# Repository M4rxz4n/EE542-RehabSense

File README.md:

# EE542-RehabSense
Rehab Sense Project for embedded systems capstone class

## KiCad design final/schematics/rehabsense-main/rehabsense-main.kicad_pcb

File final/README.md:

# RehabSense — final

Single-channel sEMG + dual-IMU armband for home-based stroke rehabilitation.
Built to PRD v1.4.

## What to flash, and what to run

```
firmware-s3/   ← FLASH THIS.  Arduino, ESP32-S3 / XIAO ESP32S3
app/           ← RUN THIS.    Flutter, iOS and Android
```

Everything else here is reference or tooling:

| Directory | What it is |
| --- | --- |
| `firmware-s3/` | **The shipping firmware.** `rehabsense_v5` retargeted from the ESP32 Dev Module to the ESP32-S3, on either of two wirings, with two haptic motors. All of FC1–FC6, FT1–FT4, AP1–AP2, GP1–GP3, AT1–AT4 |
| `app/` | **The shipping app.** Patient, calibration, session analysis, progress over time, therapist dashboard, developer tools |
| `firmware/` | The ESP-IDF tree: the PRD-shaped reference implementation. Kept for its design, its host test suites and its wire-format definitions. **Does not implement the step 1–5 behaviour**, so it is not what gets flashed |
| `python/` | The `bleak` host client and the offline analysis tools. Still the fastest way to capture raw data for tuning |
| `schematics/` | KiCad project for the custom PCB |

---

## Why there are two firmwares

The prototype firmware and the ESP-IDF firmware grew in parallel and diverged.

The **ESP-IDF tree** is architecturally what the PRD describes: tiered session
buffer in PSRAM, DSP chain with a mains notch and a median-frequency
estimator, a six-step calibration protocol, five host-side test suites. What
it does not have is any of the behaviour the demo actually shows — false-curl
rejection, fatigue indicators, auto-pause, guided pace, adaptive target.

The **prototype firmware** has all of that, and it is the only one that has
ever run on hardware with electrodes attached. So it is the one that ships,
retargeted to the S3. The ESP-IDF tree stays because its wire-format
definitions are the contract both halves are written against, and because its
design is the one the written documents describe.

They speak the same BLE protocol. That is what made the retarget tractable and
what lets the app, the HTML session viewer and `rehab_client.py` all talk to
either one.

---

## The three hosts, and when to use each

| Host | Good for | Needs |
| --- | --- | --- |
| **`app/`** (Flutter) | The demo. A session with a patient. Progress across visits | A phone |
| **HTML session viewer** (`../prototype/prototype demo final file/`) | Reading a recorded Serial Monitor log. Quick bench work next to a USB cable | Chrome or Edge |
| **`python/rehab_client.py`** | Capturing raw data for offline tuning — filter corners, thresholds, grading weights | A laptop and `pip install bleak` |

The app's Developer tab copies the sleeve's printed output to the clipboard in
exactly the viewer's input format, so a session recorded on the phone can be
read in the viewer afterwards.

---

## Getting from nothing to a working demo

1. **Flash.** `firmware-s3/README.md`. Arduino IDE, board `ESP32S3 Dev Module`
   for the breadboard. On the XIAO it is `XIAO_ESP32S3` plus
   **Tools → PSRAM → OPI PSRAM** — the default is Disabled and the boot log
   then reads `PSRAM 0 kB`, which looks exactly like a dead memory chip.
2. **Check the sleeve alone.** Serial Monitor at 115200. The banner prints the
   bus map it was built for, which is how you catch a board flashed for the
   other wiring. Both IMUs should report started; if one does not, the message
   names its bus, the address it tried, the clock it reached and which failure
   it saw.
3. **Check both motors.** Type `hm`. It says which DRV2605Ls answered and
   where each cue plays. A sleeve running on one motor keeps working and feels
   subtly wrong, so this is worth doing before anything else is judged.
4. **Check the signal.** Type `e` for the EMG test: 3 s relaxed, 3 s
   squeezing, then an SNR figure. Do this before trusting any effort
   percentage, and especially after the move from GPIO34 to GPIO4.
5. **Calibrate.** Type `c`, then `n` through the three steps, then `g`.
6. **Run the app.** `cd app && flutter pub get && flutter analyze &&
   flutter test`, then `flutter run`. Connect, and the Calibrate tab will walk
   the same three steps from the phone.

No sleeve to hand? The app's **demo mode** drives every screen with synthetic
frames and printed lines in the real wire formats.

---

## What has and has not been verified

Worth being precise about, because the two halves have been checked by very
different means.

**Firmware — compiled, not run.** Seven configurations build with zero errors
and zero warnings at `--warnings all` — two boards × two sensor buses × two
haptic topologies, minus the crossings nobody will build;
`firmware-s3/verify_build.sh` reproduces that from nothing. The default build
is the PCB's architecture. It has never been flashed. The second haptic channel is the
one piece of behaviour that is new rather than ported, so it is the first thing
to check on the bench: `hm` on the console says which DRV2605Ls answered.

**App — cross-checked, not compiled.** `flutter analyze` and `flutter test`
have not been run; there was no Dart toolchain where this was written. Instead
`app/tool/check_dart.py` verifies names, imports, members and constructor
arguments across all 41 files, and `app/tool/check_message_patterns.py`
verifies the printed-line parser against the firmware's own format strings.
Both run clean. **Run `flutter analyze && flutter test` before the demo.**

Measured, from the real builds:

| Build | Flash used | Static RAM used, of 327,680 B | Free for locals |
| --- | --- | --- | --- |
| S3 Dev Module, I2C x2 — **the breadboard** | 664,105 B (50%) | 40,092 B (12%) | 287,588 B |
| S3 Dev Module, SPI + TCA9543A — **the PCB** | 666,401 B (50%) | 40,092 B (12%) | 287,588 B |
| XIAO ESP32S3, I2C x2 | 634,116 B (18%) | 39,772 B (12%) | 287,908 B |
| XIAO, I2C x2, PSRAM OPI | 639,386 B (19%) | 40,248 B (12%) | 287,432 B |
| XIAO ESP32S3, SPI | 636,412 B (19%) | 39,772 B (12%) | 287,908 B |

The other two `verify_build.sh` compiles — the crossed haptic topologies — land
within 500 B of these. Static RAM does not move at all.

The XIAO is **not** a memory downgrade: its ESP32-S3R8 carries the same 512 KB
SRAM and 8 MB octal PSRAM as the DevKitC-1 N8R8. The firmware uses 12% of
static RAM and never touches PSRAM.

---

## Two wirings, one firmware

The PCB is the target; the breadboard is a bring-up configuration kept
alongside it. `pins.h` chooses at compile time and nothing above `imu.cpp`
knows which it got.

| | Custom PCB — the default | Breadboard |
| --- | --- | --- |
| Board | XIAO ESP32-S3 on a carrier | ESP32-S3-DevKitC-1 |
| IMUs | **one SPI bus**, a chip select each | **two I2C buses**, one each |
| Haptics | one bus + **TCA9543A** switch | two I2C buses |
| EMG | **ADS131M02** on SPI — *not yet driven* | MyoWare 2.0 on ADC1 |
| Build with | nothing | `-DRS_IMU_BUS=RS_IMU_I2C` |
| Source | `schematics/` | the wiring diagram of 1 Nov |
| Pin numbers | **provisional** — see below | from the diagram |

Both agree on two DRV2605Ls and two ERMs. The haptic topology follows the IMU
bus, so one flag selects the whole architecture.

Two I2C buses is not a preference: both BMI270 breakouts sit at 0x68 and the
DRV2605L's 0x5A has no address strap, so each bus can hold exactly one of
each.

The two motors also reach the MCU differently, and for the same reason: `0x5A`
is fixed on a DRV2605L, so two cannot answer on one bus. The breadboard gives
each its own bus. The PCB puts both behind a **TCA9543A** 2-channel I2C switch
— `haptic.kicad_sch` has one `TCA9543APWR`, two `DRV2605LDGST`s and the nets
`SDA_H1` / `SCL_H1` / `SDA_H2`, while `mcu.kicad_sch` brings out a single
`SDA` / `SCL` pair. `RS_HAPTIC_MUX` selects, and follows the IMU bus by
default, so neither board needs its own firmware.

| | Breadboard | Custom PCB |
| --- | --- | --- |
| Two DRV2605Ls reached by | two I2C buses | one bus + TCA9543A switch |
| `RS_HAPTIC_MUX` | 0 (default with I2C IMUs) | 1 (default with SPI IMUs) |

Still unmodelled, and still provisional: the SPI mode's **GPIO numbers** (the
schematic names nets, not readably pins), the **TCA9543A's strapped address**
(`haptic_begin()` scans 0x70–0x73 and reports which answered), and the PCB's
**external SPI ADC** (`CS_ADC`, `DRDY_ADC`), which would replace the MyoWare
going straight into ADC1. `mcu.kicad_sch` also uses the `XIAO_ESP32_S3`
symbol, so the PCB is a XIAO carrier board rather than a DevKitC. The I2C
mode is the one that matches wiring that exists.

## Pin map at a glance

Full reasoning in `firmware-s3/rehabsense_s3/pins.h`.

**ESP32-S3-DevKitC-1 — the breadboard, as drawn**

| Function | GPIO |
| --- | --- |
| I2C bus 0: upper-arm BMI270 `0x68` + DRV2605L `0x5A` → ERM M1 | SDA **8**, SCL **9** |
| I2C bus 1: forearm BMI270 `0x68` + DRV2605L `0x5A` → ERM M2 | SDA **17**, SCL **18** |
| MyoWare 2.0 ENV | **4** — ADC1_CH3 |
| Status LED, WS2812 | **48** (**38** on v1.1 — build `-DRS_LED_PIN=38`) |
| Start calibration | **0** (BOOT button) |
| Spare | **5** (MyoWare RAW), **6** |

One 4.7 kΩ pull-up per line per bus, to 3V3. Do not wire GPIO 0/3/45/46
(strapping), 19/20 (USB), 26–32 (flash), 33–37 (octal PSRAM), 43/44 (UART).

**XIAO ESP32S3 — the shipping sleeve.** Same build; only pins that leave the
module. Silkscreen in brackets.

| Function | GPIO |
| --- | --- |
| I2C bus 0 | SDA **5** [D4], SCL **6** [D5] |
| I2C bus 1 | SDA **8** [D9], SCL **9** [D10] |
| MyoWare 2.0 ENV | **4** [D3] |
| Status LED | **21** (plain, active LOW — the XIAO has no WS2812) |

Free on the XIAO: GPIO3 [D2] for the Phase 2 triceps channel, and GPIO43/44
[D6/D7].

On the PCB's SPI wiring each BMI270 breakout needs its **ADR jumper fully
open** — that is what selects SPI — and its I2C pull-ups cut. On the
breadboard the jumpers stay closed at 0x68 and the pull-ups stay.

---

## Open items

| Open | Blocked on |
| --- | --- |
| First flash, and a real BLE connection | A bench |
| Both BMI270s answering over SPI | A bench |
| **Any EMG at all on the PCB** | The ADS131M02 driver, which needs four numbers off the board. `ADC1` is unconnected there |
| Both DRV2605Ls answering — type `hm` | A bench. Two motors is new scope, not a port |
| Whether the pace beat belongs on the forearm alone | Someone wearing it. One column of the table in `haptic.cpp` |
| Whether the WS2812 is on GPIO48 or GPIO38 | Which DevKitC-1 revision is on the desk |
| The PCB's real pin assignment, and its external SPI ADC | Reading `schematics/`. The SPI mode's GPIO numbers are provisional and that board also moves the EMG off ADC1 |
| The TCA9543A path, and its strapped address | Never run. `haptic_begin()` scans 0x70–0x73 and says which answered |
| EMG levels on GPIO4 against the prototype's GPIO34 | Different ADC, different attenuation curve. Run `e` and compare |
| Elbow-angle accuracy | PRD gate: 5–10° against a goniometer at 0°, 45°, 90°, 135° |
| `flutter analyze` / `flutter test` | A machine with the Flutter SDK |
| Battery endurance | A two-hour run |
| Haptic feel on the final ERM | DRV2605L values carried over from a different motor mounting |
| Filter corners, thresholds, grading weights | Volunteer data. All settable over BLE at runtime, so tuning is a session rather than a rebuild |

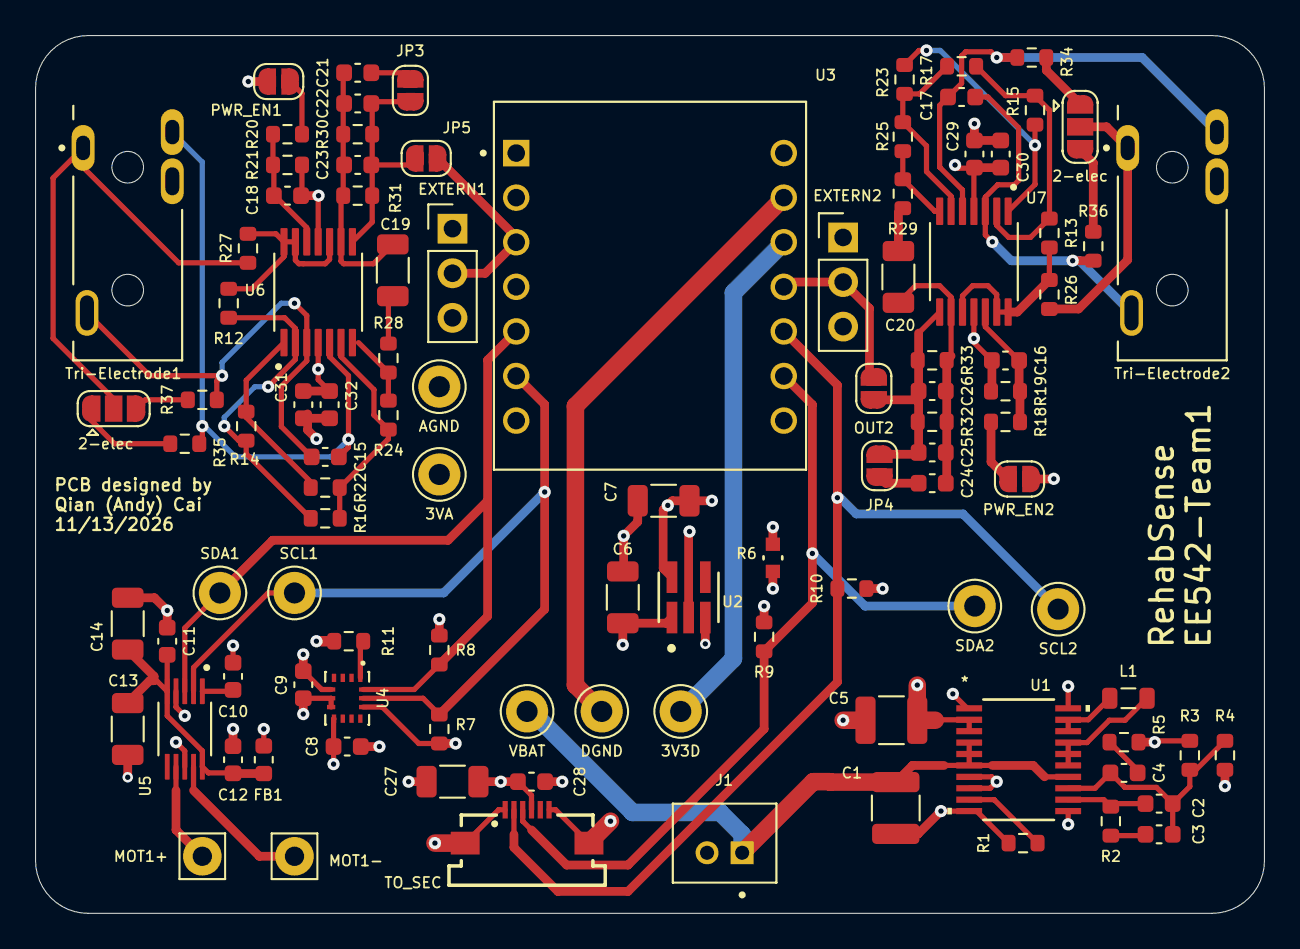
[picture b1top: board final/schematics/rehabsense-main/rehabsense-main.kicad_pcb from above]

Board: 4 copper layers, 70.0 x 50.0 mm, 103 parts (0 on the bottom side), 55 nets.

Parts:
2-elec, 2-elec#2: SolderJumper_3_Open; SolderJumper-3_P1.3mm_Open_RoundedPad1.0x1.5mm
3V3D, 3VA: TestPoint; Pin_D1.0mm_L10.0mm_LooseFit
AGND: TestPoint; Pin_D1.0mm_L10.0mm_LooseFit
C1: 47uF 10V; C_1210_3225Metric
C2: 12pF; C_0603_1608Metric
C3: 680pF; C_0603_1608Metric
C4: 47pF; C_0603_1608Metric
C5: 100uF 6.3V; C_1210_3225Metric
C6, C7: 1uF 10V; C_1206_3216Metric
C8, C9: 0.1uF; C_0603_1608Metric
C10: 1uF; C_0603_1608Metric
C11: 1uF 6.3V; C_0603_1608Metric
C12, C28: 0.1uF 6.3V; C_0603_1608Metric
C13, C27: 10uF 6.3V; C_1206_3216Metric
C14: 100uF 6.3V; C_1206_3216Metric
C15, C17: 2.2nF; C_0603_1608Metric
C16, C18: 220nF; C_0603_1608Metric
C19, C20: 47uF; C_1206_3216Metric
C21, C23, C24, C26: 47nF; C_0603_1608Metric
C22, C25: BPFC_C; C_0603_1608Metric
C29, C31: 100nF; C_0603_1608Metric
C30, C32: 4.7uF; C_0603_1608Metric
DGND: TestPoint; Pin_D1.0mm_L10.0mm_LooseFit
EXTERN1, EXTERN2: Conn_01x03_Pin; PinHeader_1x03_P2.54mm_Vertical
FB1: FerriteBead; L_0603_1608Metric
J1: B2B-PH-K-S; JST_B2B-PH-K-S
JP3, JP4, JP5: SolderJumper_2_Open; SolderJumper-2_P1.3mm_Open_RoundedPad1.0x1.5mm
L1: 2.2uH; L_0805_2012Metric
MOT1+: MOT1+; Pin_D1.1mm_L8.5mm_W2.5mm_FlatFork
MOT1-: MOT1-; Pin_D1.1mm_L8.5mm_W2.5mm_FlatFork
OUT2: SolderJumper_2_Open; SolderJumper-2_P1.3mm_Open_RoundedPad1.0x1.5mm
PWR_EN1, PWR_EN2: SolderJumper_2_Open; SolderJumper-2_P1.3mm_Open_RoundedPad1.0x1.5mm
R1: 90.9k; R_0603_1608Metric
R2: 49.9k; R_0603_1608Metric
R3: 825k; R_0603_1608Metric
R4: 182k; R_0603_1608Metric
R5: 6.49k; R_0603_1608Metric
R6: 0R; RC0603N_YAG
R7, R8, R9, R10: 2.2k; R_0603_1608Metric
R11: 100k; R_0603_1608Metric
R12, R13, R18, R19, R20, R21, R24, R25: 10k; R_0603_1608Metric
R14, R15, R22, R23, R26, R27, R28, R29: 1k; R_0603_1608Metric
R16, R17: RG; R_0603_1608Metric
R30, R32: BPFC_R; R_0603_1608Metric
R31, R33, R34, R35, R36, R37: 1M; R_0603_1608Metric
SCL1, SCL2: TestPoint; Pin_D1.0mm_L10.0mm_LooseFit
SDA1, SDA2: TestPoint; Pin_D1.0mm_L10.0mm_LooseFit
TO_SEC: 6871XX183622_687106183622; 687106183622
Tri-Electrode1, Tri-Electrode2: SJ3-35083C-TR; SAMESKY_SJ3-35083C-TR
U1: LTC3113EFE-TRPBF; TSSOP-20_FE&slash_CA_LIT
U2: TPS7A2030PDBVR; DBV0005A-IPC_A
U3: XIAO_ESP32_S3; MODULE_XIAO_ESP32_S3
U4: BMI270; XDCR_BMI270
U5: DRV2605LDGST; SOP50P490X110-10N
U6, U7: OPA4322AIPWR; SOP65P640X120-14N
VBAT: TestPoint; Pin_D1.0mm_L10.0mm_LooseFit

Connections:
+3V3D: 3V3D.1 (1_1), C5.1, C6.1, C8.1, C9.1, C27.1, C28.1, FB1.1, R3.2, R5.2, R7.1, R8.1, R9.1, R10.1, TO_SEC.4, U1.2 (VOUT), U1.3 (VOUT), U2.1 (IN), U2.3 (EN), U3.12 (3V3), U4.5 (VDDIO), U4.8 (VDD), U4.12 (CSB)
+3VA: 3VA.1 (1_1), C7.1, C29.2, C30.2, C31.2, C32.2, EXTERN1.1, EXTERN2.1, PWR_EN1.2 (B), PWR_EN2.2 (B), U2.5 (OUT), U6.4, U7.4
+BATT: C1.1, J1.1, U1.4 (VIN), U1.5 (VIN), U1.6 (VIN), U1.14 (RUN), VBAT.1 (1_1)
+VMOT: C11.1, C12.1, C13.1, C14.1, FB1.2, U5.5 (EN), U5.10 (VDD)
/emg/OUT1: C22.2, C23.2, JP3.1 (A), JP5.2 (B), R30.2, R31.2, U6.8
/emg/OUT2: C25.2, C26.2, JP4.1 (A), OUT2.2 (B), R32.2, R33.2, U7.8
/emg/ampref1: R12.1, R27.1, U6.10, U6.13, U6.14
/emg/ampref2: R13.1, R26.1, U7.10, U7.13, U7.14
/emg/bpfIN1: C19.2, C21.1, C22.1, C23.1, R30.1, R31.1, U6.9
/emg/bpfIN2: C20.2, C24.1, C25.1, C26.1, R32.1, R33.1, U7.9
/emg/inaOUT1: R24.2, R28.1, U6.7
/emg/inaOUT2: R25.2, R29.1, U7.7
/haptic/MOT1+: MOT1+.1 (1_1), U5.7 (OUT+)
/haptic/MOT1-: MOT1-.1 (1_1), U5.9 (OUT-)
ADC1: EXTERN1.2, JP5.1 (A), U3.3 (D2/GPIO3)
ADC2: EXTERN2.2, OUT2.1 (A), U3.11 (D10/GPIO9)
AGND: AGND.1 (1_1), C6.2, C7.2, C16.1, C18.1, C29.1, C30.1, C31.1, C32.1, EXTERN1.3, EXTERN2.3, R6.2, R19.1, R21.1, U2.2 (GND), U6.11, U7.11
DGND: C1.2, C5.2, C8.2, C9.2, C10.2, C11.2, C12.2, C13.2, C14.2, C27.2, C28.2, DGND.1 (1_1), J1.2, R1.1, R4.1, R6.1, R11.2, TO_SEC.1, TO_SEC.6, TO_SEC.Z1, TO_SEC.Z2, U1.1 (PGND), U1.7 (SGND), U1.8 (BURST), U1.10 (PGND), U1.11 (PGND), U1.20 (PGND), U3.13 (GND), U4.6 (GNDIO), U4.7 (GND), U5.4 (IN/TRIG), U5.8 (GND)
DRL1: 2-elec.2 (C), R27.2, Tri-Electrode1.1
DRL2: 2-elec#2.2 (C), R26.2, Tri-Electrode2.1
IN1+: C15.1, R37.2, Tri-Electrode1.2, U6.3
IN1-: C15.2, R35.1, Tri-Electrode1.4, U6.5
IN2+: C17.1, R36.2, Tri-Electrode2.2, U7.3
IN2-: C17.2, R34.1, Tri-Electrode2.4, U7.5
unnamed: C3.1, R2.2
unnamed: C4.2, R5.1
unnamed: C16.2, R18.1, R19.2, U7.12
unnamed: C18.2, R20.1, R21.2, U6.12
unnamed: C19.1, R28.2
unnamed: C20.1, R29.2
unnamed: PWR_EN2.1 (A), R18.2
unnamed: PWR_EN1.1 (A), R20.2
unnamed: C21.2, JP3.2 (B)
unnamed: C24.2, JP4.2 (B)
unnamed: 2-elec#2.1 (A), R34.2
unnamed: 2-elec#2.3 (B), R36.1
unnamed: 2-elec.1 (A), R35.2
unnamed: 2-elec.3 (B), R37.1
unnamed: L1.1, U1.18 (SW2), U1.19 (SW2)
unnamed: L1.2, U1.15 (SW1), U1.16 (SW1), U1.17 (SW1)
unnamed: R12.2, R14.1, R16.1, U6.2
unnamed: R13.2, R15.1, R17.1, U7.2
unnamed: R14.2, R22.1, U6.1
unnamed: R15.2, R23.1, U7.1
unnamed: R16.2, R22.2, R24.1, U6.6
unnamed: R17.2, R23.2, R25.1, U7.6
unnamed: C2.2, C3.2, C4.1, R3.1, R4.2, U1.13 (FB)
unnamed: R1.2, U1.9 (RT)
unnamed: C2.1, R2.1, U1.12 (VC)
unnamed: R11.1, U4.1 (SDO)
unnamed: C10.1, U5.1 (REG)
SCL0: R7.2, SCL1.1 (1_1), U3.6 (D5/GPIO6), U4.13 (SCX), U5.2 (SCL)
SCL1: R10.2, SCL2.1 (1_1), TO_SEC.2, U3.10 (D9/GPIO8)
SDA0: R8.2, SDA1.1 (1_1), U3.5 (D4/GPIO5), U4.14 (SDX), U5.3 (SDA)
SDA1: R9.2, SDA2.1 (1_1), TO_SEC.3, U3.9 (D8/GPIO7)

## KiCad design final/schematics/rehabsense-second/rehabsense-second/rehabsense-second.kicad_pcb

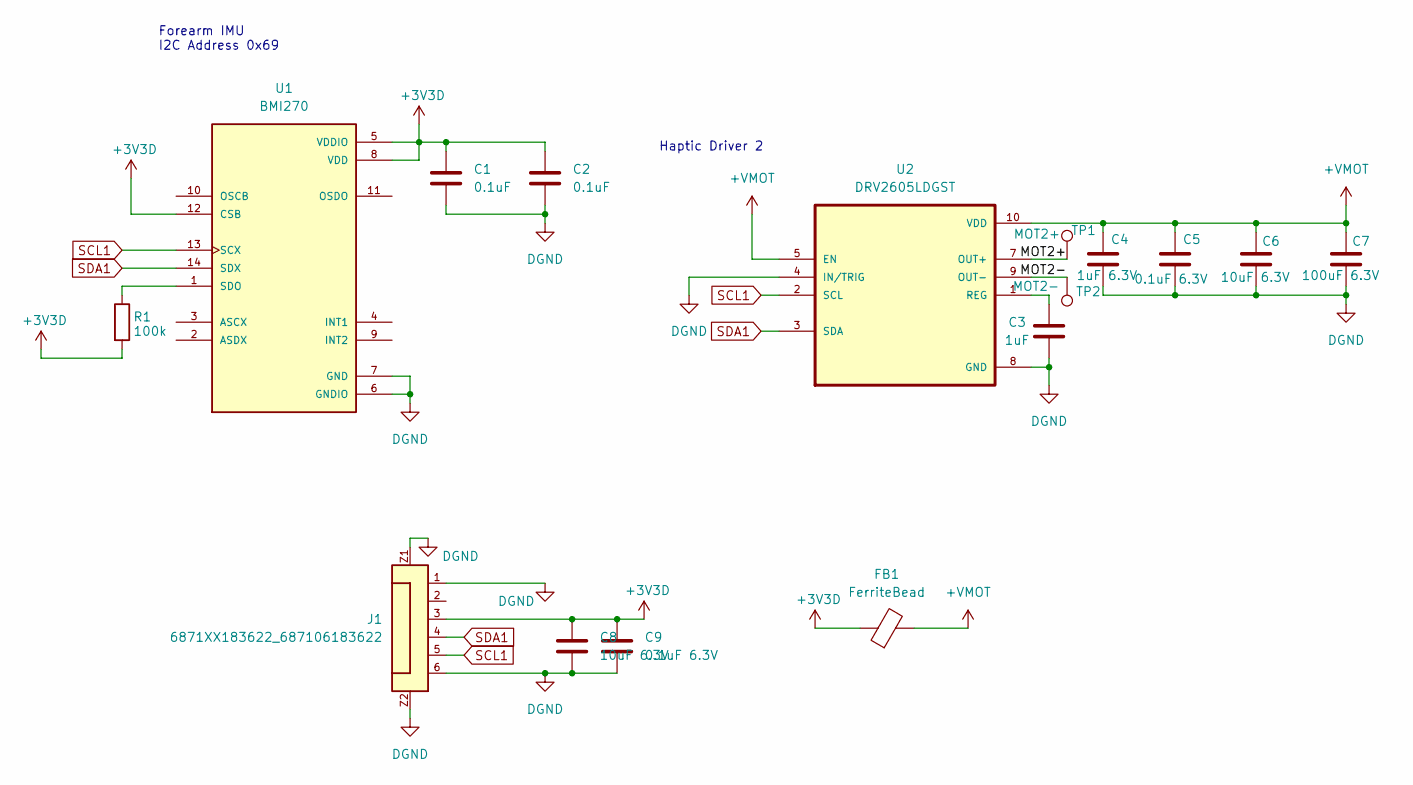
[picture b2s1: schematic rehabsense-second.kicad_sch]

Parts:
C1, C2: 0.1uF; C_0603_1608Metric
C3: 1uF; C_0603_1608Metric
C4: 1uF 6.3V; C_0603_1608Metric
C5, C9: 0.1uF 6.3V; C_0603_1608Metric
C6: 10uF 6.3V; C_1206_3216Metric
C7: 100uF 6.3V; C_1206_3216Metric
C8: 10uF 6.3V; C_0603_1608Metric
FB1: FerriteBead; L_0603_1608Metric
J1: 6871XX183622_687106183622; 687106183622; MPN 687106183622
R1: 100k; R_0603_1608Metric
TP1: MOT2+; Pin_D1.1mm_L8.5mm_W2.5mm_FlatFork
TP2: MOT2-; Pin_D1.1mm_L8.5mm_W2.5mm_FlatFork
U1: BMI270; XDCR_BMI270
U2: DRV2605LDGST; SOP50P490X110-10N

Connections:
+3V3D: C1.1, C2.1, C8.1, C9.1, FB1.1, J1.3, R1.2, U1.5 (VDDIO), U1.8 (VDD), U1.12 (CSB); also elsewhere on the board
+VMOT: C4.1, C5.1, C6.1, C7.1, FB1.2, U2.5 (EN), U2.10 (VDD)
/MOT2+: TP1.1 (1_1), U2.7 (OUT+)
/MOT2-: TP2.1 (1_1), U2.9 (OUT-)
DGND: C1.2, C2.2, C3.2, C4.2, C5.2, C6.2, C7.2, C8.2, C9.2, J1.1, J1.6, J1.Z1, J1.Z2, U1.6 (GNDIO), U1.7 (GND), U2.4 (IN/TRIG), U2.8 (GND); also elsewhere on the board
unnamed: R1.1, U1.1 (SDO)
unnamed: C3.1, U2.1 (REG)
SCL1: J1.5, U1.13 (SCX), U2.2 (SCL); also elsewhere on the board
SDA1: J1.4, U1.14 (SDX), U2.3 (SDA); also elsewhere on the board

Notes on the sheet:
Haptic Driver 2
Forearm IMU I2C Address 0x69

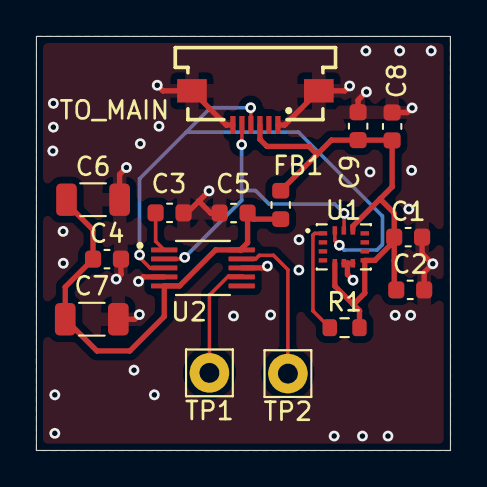
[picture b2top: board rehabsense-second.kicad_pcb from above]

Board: 2 copper layers, 23.0 x 23.0 mm, 16 parts (0 on the bottom side), 9 nets.

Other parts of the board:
TO_MAIN: 6871XX183622_687106183622; 687106183622

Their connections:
+3V3D: TO_MAIN.3; also elsewhere on the board
DGND: TO_MAIN.1, TO_MAIN.6, TO_MAIN.Z1, TO_MAIN.Z2; also elsewhere on the board
SCL1: TO_MAIN.5; also elsewhere on the board
SDA1: TO_MAIN.4; also elsewhere on the board

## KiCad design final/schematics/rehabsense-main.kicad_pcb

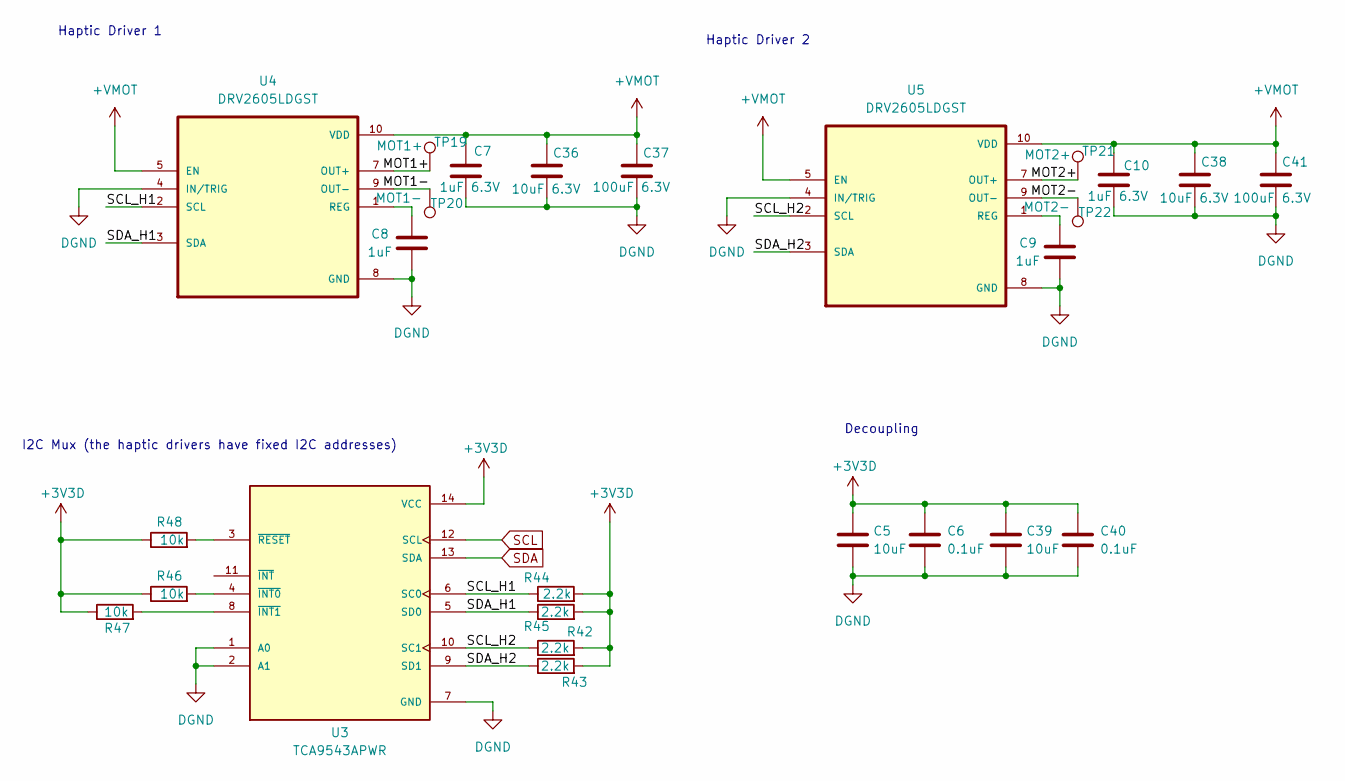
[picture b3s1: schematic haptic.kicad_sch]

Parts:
C5, C39: 10uF; C_0603_1608Metric
C6, C40: 0.1uF; C_0603_1608Metric
C7, C10: 1uF 6.3V; C_0603_1608Metric
C8, C9: 1uF; C_0603_1608Metric
C36, C38: 10uF 6.3V; C_1206_3216Metric
C37, C41: 100uF 6.3V; C_1206_3216Metric
R42, R43, R44, R45: 2.2k; R_0603_1608Metric
R46, R47, R48: 10k; R_0603_1608Metric
TP19: MOT1+; Pin_D1.1mm_L8.5mm_W2.5mm_FlatFork
TP20: MOT1-; Pin_D1.1mm_L8.5mm_W2.5mm_FlatFork
TP21: MOT2+; Pin_D1.1mm_L8.5mm_W2.5mm_FlatFork
TP22: MOT2-; Pin_D1.1mm_L8.5mm_W2.5mm_FlatFork
U3: TCA9543APWR; IC_TCA9543APWR; PARTREV B
U4, U5: DRV2605LDGST; SOP50P490X110-10N

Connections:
+3V3D: C5.1, C6.1, C39.1, C40.1, R42.2, R43.2, R44.2, R45.2, R46.1, R47.1, R48.1, U3.14 (VCC); also elsewhere on the board
+VMOT: C7.1, C10.1, C36.1, C37.1, C38.1, C41.1, U4.5 (EN), U4.10 (VDD), U5.5 (EN), U5.10 (VDD); also elsewhere on the board
/haptic/MOT1+: TP19.1 (1_1), U4.7 (OUT+)
/haptic/MOT1-: TP20.1 (1_1), U4.9 (OUT-)
/haptic/MOT2+: TP21.1 (1_1), U5.7 (OUT+)
/haptic/MOT2-: TP22.1 (1_1), U5.9 (OUT-)
/haptic/SCL_H1: R44.1, U3.6 (SC0), U4.2 (SCL)
/haptic/SCL_H2: R42.1, U3.10 (SC1), U5.2 (SCL)
/haptic/SDA_H1: R45.1, U3.5 (SD0), U4.3 (SDA)
/haptic/SDA_H2: R43.1, U3.9 (SD1), U5.3 (SDA)
DGND: C5.2, C6.2, C7.2, C8.2, C9.2, C10.2, C36.2, C37.2, C38.2, C39.2, C40.2, C41.2, U3.1 (A0), U3.2 (A1), U3.7 (GND), U4.4 (IN/TRIG), U4.8 (GND), U5.4 (IN/TRIG), U5.8 (GND); also elsewhere on the board
unnamed: R46.2, U3.4 (~INT0)
unnamed: R47.2, U3.8 (~INT1)
unnamed: R48.2, U3.3 (~RESET)
unnamed: C8.1, U4.1 (REG)
unnamed: C9.1, U5.1 (REG)
SCL: U3.12 (SCL); also elsewhere on the board
SDA: U3.13 (SDA); also elsewhere on the board

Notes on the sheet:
Decoupling
Haptic Driver 2
I2C Mux (the haptic drivers have fixed I2C addresses)
Haptic Driver 1

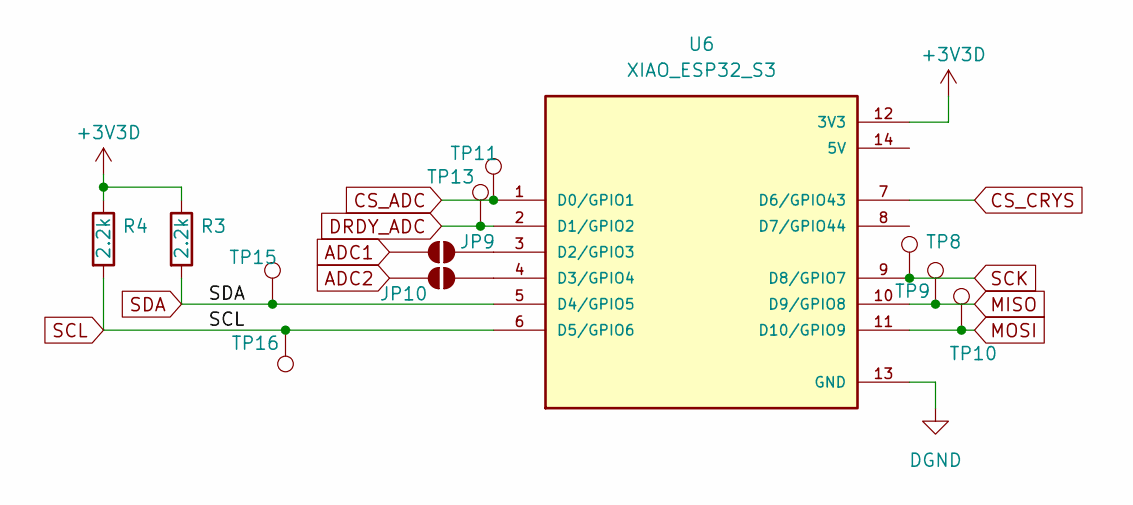
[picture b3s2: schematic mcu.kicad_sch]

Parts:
JP9, JP10: SolderJumper_2_Open; SolderJumper-2_P1.3mm_Open_RoundedPad1.0x1.5mm
R3, R4: 2.2k; R_0603_1608Metric
TP8, TP9, TP10, TP11, TP13, TP15, TP16: TestPoint; Pin_D1.0mm_L10.0mm_LooseFit
U6: XIAO_ESP32_S3; MODULE_XIAO_ESP32_S3; PARTREV April 22nd, 2026

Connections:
+3V3D: R3.1, R4.1, U6.12 (3V3); also elsewhere on the board
ADC1: JP9.2 (B); also elsewhere on the board
ADC2: JP10.2 (B); also elsewhere on the board
CS_ADC: TP11.1 (1_1), U6.1 (D0/GPIO1); also elsewhere on the board
CS_CRYS: U6.7 (D6/GPIO43)
DGND: U6.13 (GND); also elsewhere on the board
DRDY_ADC: TP13.1 (1_1), U6.2 (D1/GPIO2)
MISO: TP9.1 (1_1), U6.10 (D9/GPIO8); also elsewhere on the board
MOSI: TP10.1 (1_1), U6.11 (D10/GPIO9); also elsewhere on the board
unnamed: JP9.1 (A), U6.3 (D2/GPIO3)
unnamed: JP10.1 (A), U6.4 (D3/GPIO4)
SCK: TP8.1 (1_1), U6.9 (D8/GPIO7); also elsewhere on the board
SCL: R4.2, TP16.1 (1_1), U6.6 (D5/GPIO6); also elsewhere on the board
SDA: R3.2, TP15.1 (1_1), U6.5 (D4/GPIO5); also elsewhere on the board

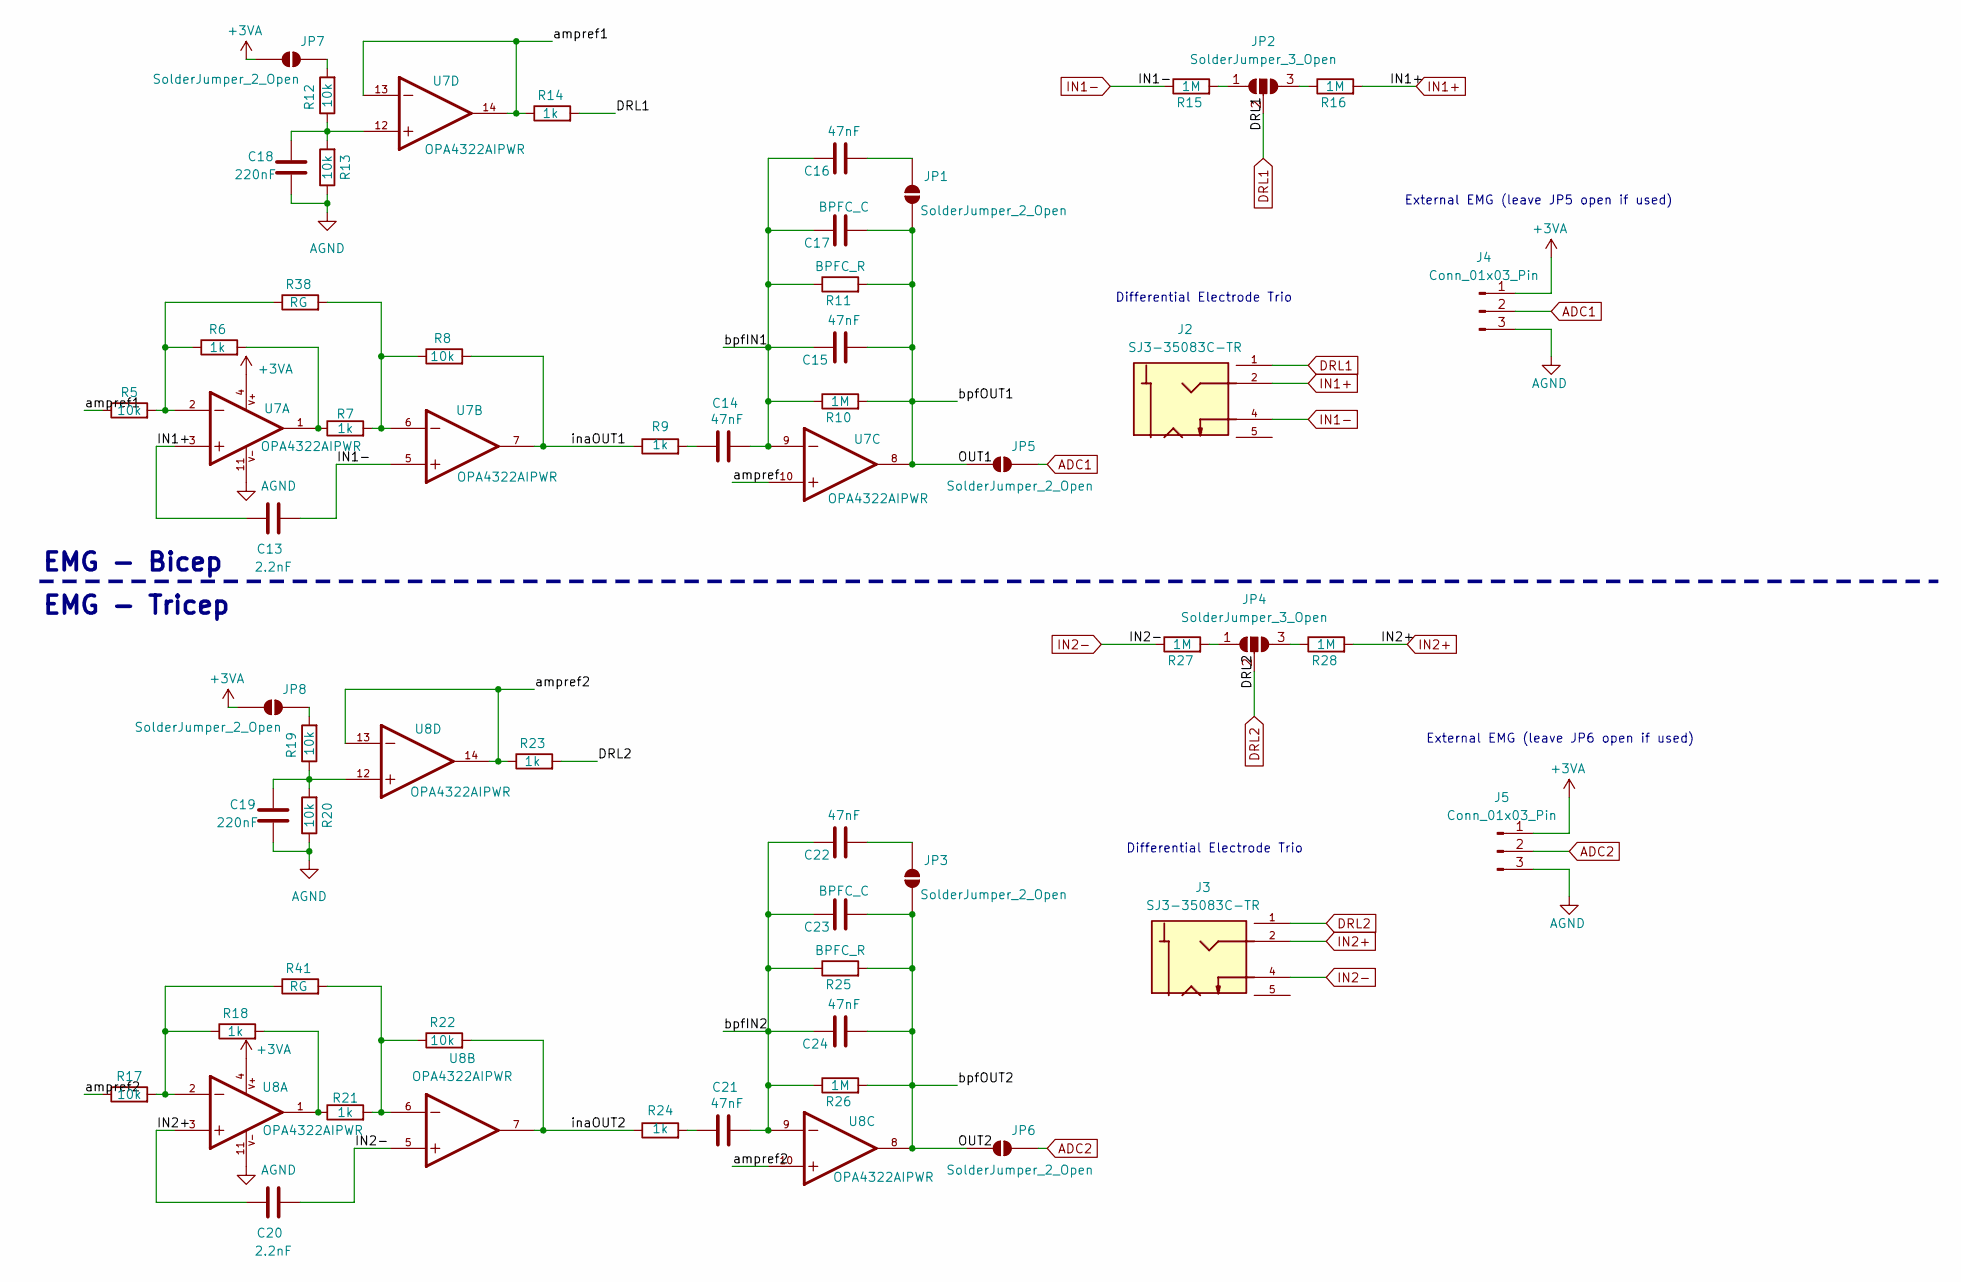
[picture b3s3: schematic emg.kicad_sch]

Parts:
C13, C20: 2.2nF; C_0603_1608Metric
C14, C15, C16, C21, C22, C24: 47nF; C_0603_1608Metric
C17, C23: BPFC_C; C_0603_1608Metric
C18, C19: 220nF; C_0603_1608Metric
J2, J3: SJ3-35083C-TR; SAMESKY_SJ3-35083C-TR; PARTREV 1.01
J4, J5: Conn_01x03_Pin; PinHeader_1x03_P1.00mm_Vertical
JP1, JP3, JP5, JP6, JP7, JP8: SolderJumper_2_Open; SolderJumper-2_P1.3mm_Open_RoundedPad1.0x1.5mm
JP2, JP4: SolderJumper_3_Open; SolderJumper-3_P1.3mm_Open_RoundedPad1.0x1.5mm
R5, R8, R12, R13, R17, R19, R20, R22: 10k; R_0603_1608Metric
R6, R7, R9, R14, R18, R21, R23, R24: 1k; R_0603_1608Metric
R10, R15, R16, R26, R27, R28: 1M; R_0603_1608Metric
R11, R25: BPFC_R; R_0603_1608Metric
R38, R41: RG; R_0603_1608Metric
U7, U8: OPA4322AIPWR; SOP65P640X120-14N; MPN OPA4322AIPWR

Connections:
+3VA: J4.1, J5.1, JP7.2 (B), JP8.2 (B), U7.4, U8.4; also elsewhere on the board
/emg/OUT1: C15.2, C17.2, JP1.1 (A), JP5.2 (B), R10.2, R11.2, U7.8
/emg/OUT2: C23.2, C24.2, JP3.1 (A), JP6.2 (B), R25.2, R26.2, U8.8
/emg/ampref: U7.10
/emg/ampref1: R5.1, R14.1, U7.13, U7.14
/emg/ampref2: R17.1, R23.1, U8.10, U8.13, U8.14
/emg/bpfIN1: C14.2, C15.1, C16.1, C17.1, R10.1, R11.1, U7.9
/emg/bpfIN2: C21.2, C22.1, C23.1, C24.1, R25.1, R26.1, U8.9
/emg/inaOUT1: R8.2, R9.1, U7.7
/emg/inaOUT2: R22.2, R24.1, U8.7
ADC1: J4.2, JP5.1 (A); also elsewhere on the board
ADC2: J5.2, JP6.1 (A); also elsewhere on the board
AGND: C18.1, C19.1, J4.3, J5.3, R13.1, R20.1, U7.11, U8.11; also elsewhere on the board
DRL1: J2.1, JP2.2 (C), R14.2
DRL2: J3.1, JP4.2 (C), R23.2
IN1+: C13.1, J2.2, R16.2, U7.3
IN1-: C13.2, J2.4, R15.1, U7.5
IN2+: C20.1, J3.2, R28.2, U8.3
IN2-: C20.2, J3.4, R27.1, U8.5
unnamed: C14.1, R9.2
unnamed: C18.2, R12.1, R13.2, U7.12
unnamed: C19.2, R19.1, R20.2, U8.12
unnamed: C21.1, R24.2
unnamed: C16.2, JP1.2 (B)
unnamed: JP2.1 (A), R15.2
unnamed: JP2.3 (B), R16.1
unnamed: C22.2, JP3.2 (B)
unnamed: JP4.1 (A), R27.2
unnamed: JP4.3 (B), R28.1
unnamed: JP7.1 (A), R12.2
unnamed: JP8.1 (A), R19.2
unnamed: R6.2, R7.1, U7.1
unnamed: R17.2, R18.1, R41.1, U8.2
unnamed: R18.2, R21.1, U8.1
unnamed: R21.2, R22.1, R41.2, U8.6
unnamed: R5.2, R6.1, R38.1, U7.2
unnamed: R7.2, R8.1, R38.2, U7.6

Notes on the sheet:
EMG - Tricep
EMG - Bicep
Differential Electrode Trio
External EMG (leave JP5 open if used)
External EMG (leave JP6 open if used)

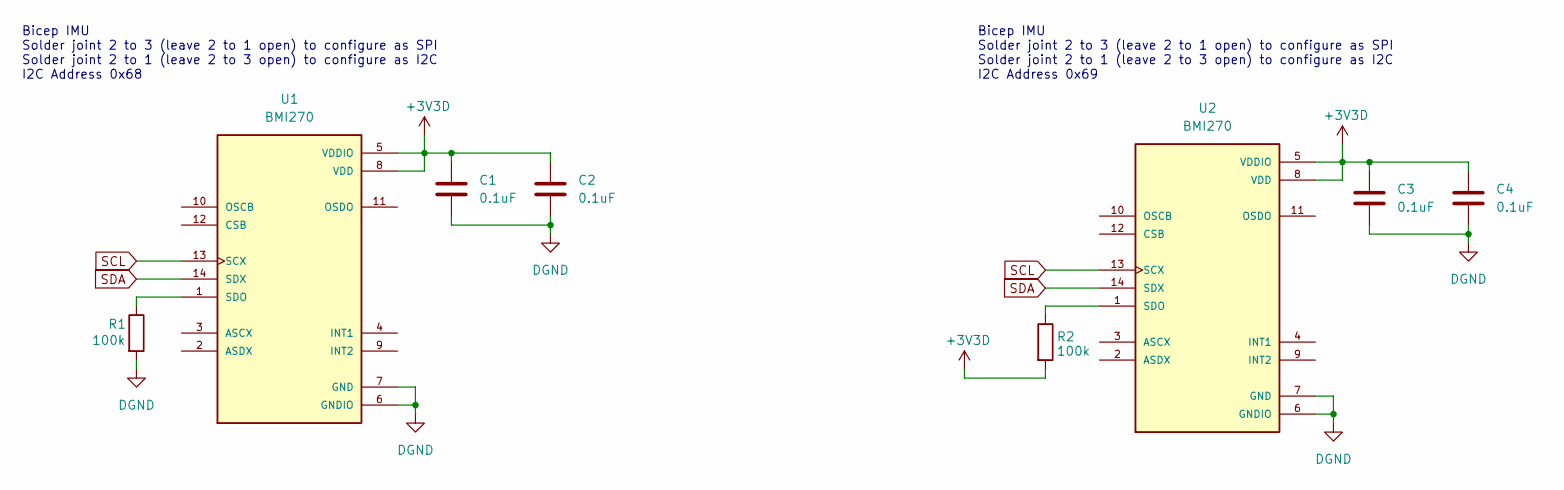
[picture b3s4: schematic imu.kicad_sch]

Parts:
C1, C2, C3, C4: 0.1uF; C_0603_1608Metric
R1, R2: 100k; R_0603_1608Metric
U1, U2: BMI270; XDCR_BMI270

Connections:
+3V3D: C1.1, C2.1, C3.1, C4.1, R2.2, U1.5 (VDDIO), U1.8 (VDD), U2.5 (VDDIO), U2.8 (VDD); also elsewhere on the board
DGND: C1.2, C2.2, C3.2, C4.2, R1.2, U1.6 (GNDIO), U1.7 (GND), U2.6 (GNDIO), U2.7 (GND); also elsewhere on the board
unnamed: R1.1, U1.1 (SDO)
unnamed: R2.1, U2.1 (SDO)
SCL: U1.13 (SCX), U2.13 (SCX); also elsewhere on the board
SDA: U1.14 (SDX), U2.14 (SDX); also elsewhere on the board

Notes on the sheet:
Bicep IMU Solder joint 2 to 3 (leave 2 to 1 open) to configure as SPI Solder joint 2 to 1 (leave 2 to 3 open) to configure as I2C I2C Address 0x69
Bicep IMU Solder joint 2 to 3 (leave 2 to 1 open) to configure as SPI Solder joint 2 to 1 (leave 2 to 3 open) to configure as I2C I2C Address 0x68

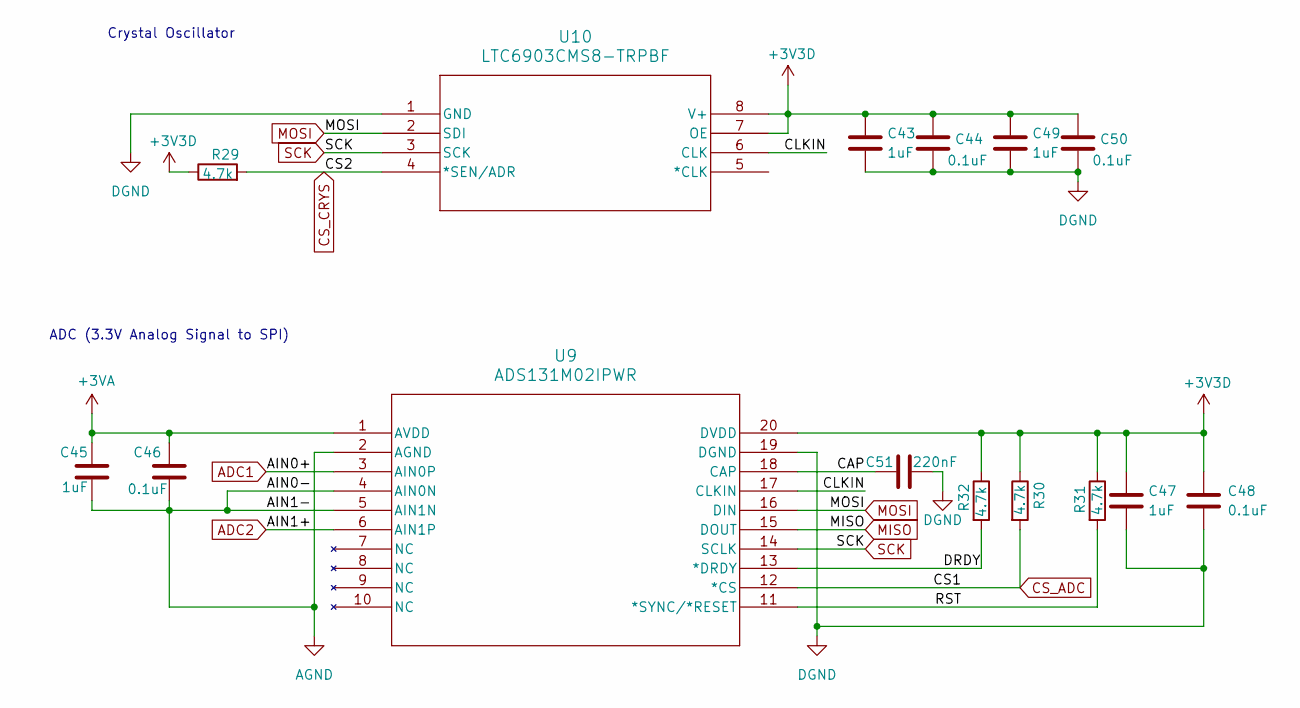
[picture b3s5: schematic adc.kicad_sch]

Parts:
C43, C45, C47, C49: 1uF; C_0603_1608Metric
C44, C46, C48, C50: 0.1uF; C_0603_1608Metric
C51: 220nF; C_0603_1608Metric
R29, R30, R31, R32: 4.7k; R_0603_1608Metric
U9: ADS131M02IPWR; TSSOP20_PW_TEX
U10: LTC6903CMS8-TRPBF; MSOP-8_MS_LIT

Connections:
+3V3D: C43.1, C44.1, C47.1, C48.1, C49.1, C50.1, R29.1, R30.1, R31.1, R32.1, U9.20 (DVDD), U10.7 (OE), U10.8 (V+); also elsewhere on the board
+3VA: C45.1, C46.1, U9.1 (AVDD); also elsewhere on the board
/adc (DNP)/CAP: C51.1, U9.18 (CAP)
/adc (DNP)/CLKIN: U9.17 (CLKIN), U10.6 (CLK)
/adc (DNP)/DRDY: R32.2, U9.13 (*DRDY)
/adc (DNP)/RST: R31.2, U9.11 (*SYNC/*RESET)
ADC1: U9.3 (AIN0P); also elsewhere on the board
ADC2: U9.6 (AIN1P); also elsewhere on the board
AGND: C45.2, C46.2, U9.2 (AGND), U9.4 (AIN0N), U9.5 (AIN1N); also elsewhere on the board
CS_ADC: R30.2, U9.12 (*CS); also elsewhere on the board
DGND: C43.2, C44.2, C47.2, C48.2, C49.2, C50.2, C51.2, U9.19 (DGND), U10.1 (GND); also elsewhere on the board
MISO: U9.15 (DOUT); also elsewhere on the board
MOSI: U9.16 (DIN), U10.2 (SDI); also elsewhere on the board
unnamed: R29.2, U10.4 (*SEN/ADR)
SCK: U9.14 (SCLK), U10.3 (SCK); also elsewhere on the board

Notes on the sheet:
ADC (3.3V Analog Signal to SPI)
Crystal Oscillator

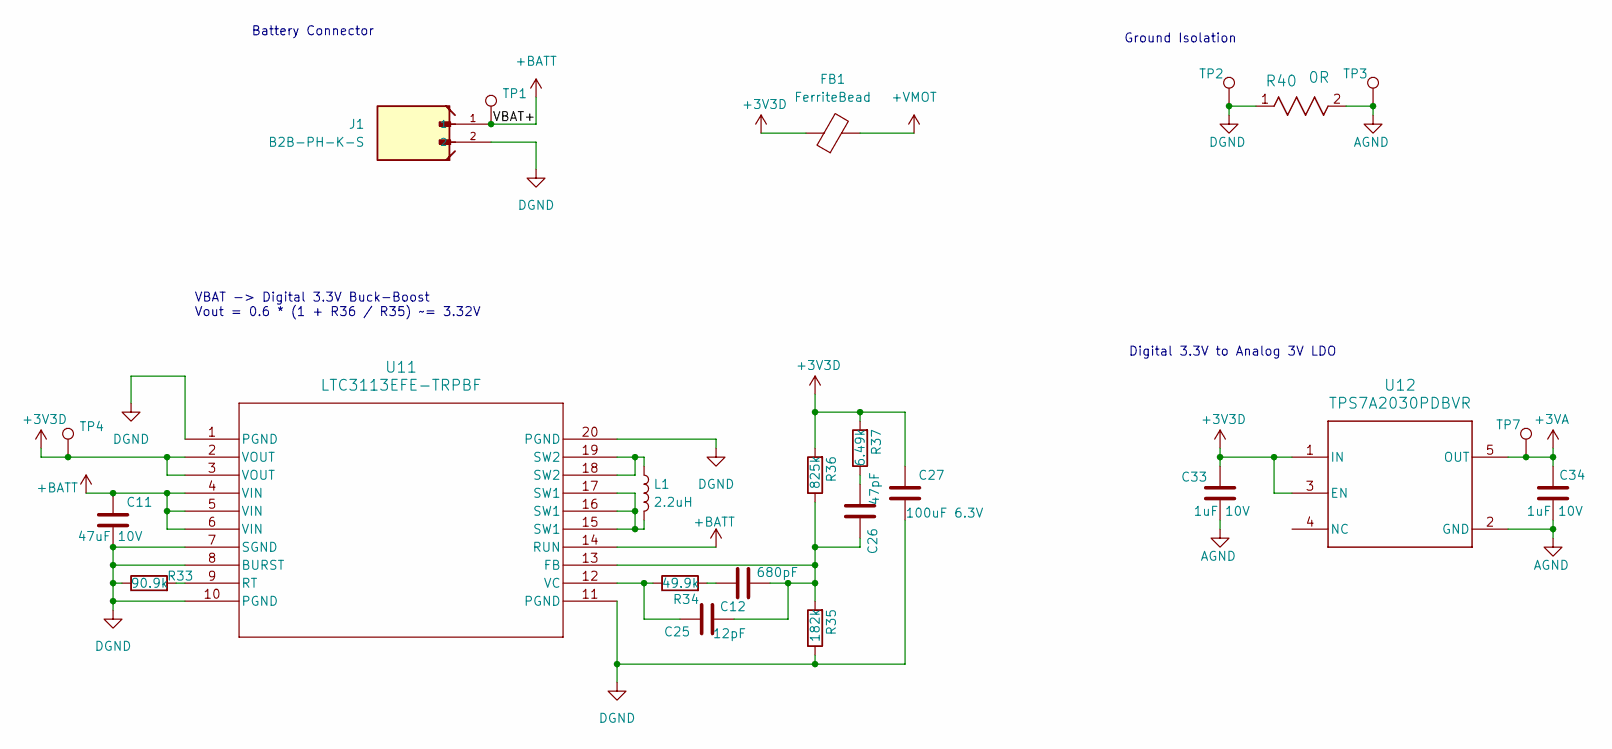
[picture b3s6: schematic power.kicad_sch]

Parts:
C11: 47uF 10V; C_1210_3225Metric
C12: 680pF; C_0603_1608Metric
C25: 12pF; C_0603_1608Metric
C26: 47pF; C_0603_1608Metric
C27: 100uF 6.3V; C_1210_3225Metric
C33, C34: 1uF 10V; C_1206_3216Metric
FB1: FerriteBead; L_0603_1608Metric
J1: B2B-PH-K-S; JST_B2B-PH-K-S
L1: 2.2uH; L_0805_2012Metric
R33: 90.9k; R_0603_1608Metric
R34: 49.9k; R_0603_1608Metric
R35: 182k; R_0603_1608Metric
R36: 825k; R_0603_1608Metric
R37: 6.49k; R_0603_1608Metric
R40: 0R; RC0603N_YAG
TP1, TP2, TP3, TP4, TP7: TestPoint; Pin_D1.0mm_L10.0mm_LooseFit
U11: LTC3113EFE-TRPBF; TSSOP-20_FE&slash_CA_LIT
U12: TPS7A2030PDBVR; DBV0005A-IPC_A

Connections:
+3V3D: C27.1, C33.1, FB1.1, R36.2, R37.2, TP4.1 (1_1), U11.2 (VOUT), U11.3 (VOUT), U12.1 (IN), U12.3 (EN); also elsewhere on the board
+3VA: C34.1, TP7.1 (1_1), U12.5 (OUT); also elsewhere on the board
+BATT: C11.1, J1.1, TP1.1 (1_1), U11.4 (VIN), U11.5 (VIN), U11.6 (VIN), U11.14 (RUN)
+VMOT: FB1.2; also elsewhere on the board
AGND: C33.2, C34.2, R40.2, TP3.1 (1_1), U12.2 (GND); also elsewhere on the board
DGND: C11.2, C27.2, J1.2, R33.1, R35.1, R40.1, TP2.1 (1_1), U11.1 (PGND), U11.7 (SGND), U11.8 (BURST), U11.10 (PGND), U11.11 (PGND), U11.20 (PGND); also elsewhere on the board
unnamed: C12.1, R34.2
unnamed: C26.2, R37.1
unnamed: L1.1, U11.18 (SW2), U11.19 (SW2)
unnamed: L1.2, U11.15 (SW1), U11.16 (SW1), U11.17 (SW1)
unnamed: C12.2, C25.2, C26.1, R35.2, R36.1, U11.13 (FB)
unnamed: R33.2, U11.9 (RT)
unnamed: C25.1, R34.1, U11.12 (VC)

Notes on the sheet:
Ground Isolation
Digital 3.3V to Analog 3V LDO
VBAT -> Digital 3.3V Buck-Boost Vout = 0.6 * (1 + R36 / R35) ~= 3.32V
Battery Connector

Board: 2 copper layers, 136 parts (0 on the bottom side), 76 nets, no tracks yet.
